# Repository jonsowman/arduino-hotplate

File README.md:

# Arduino Hotplate

An Arduino controlled hotplate for reflow soldering and rework.

Jon Sowman 2017

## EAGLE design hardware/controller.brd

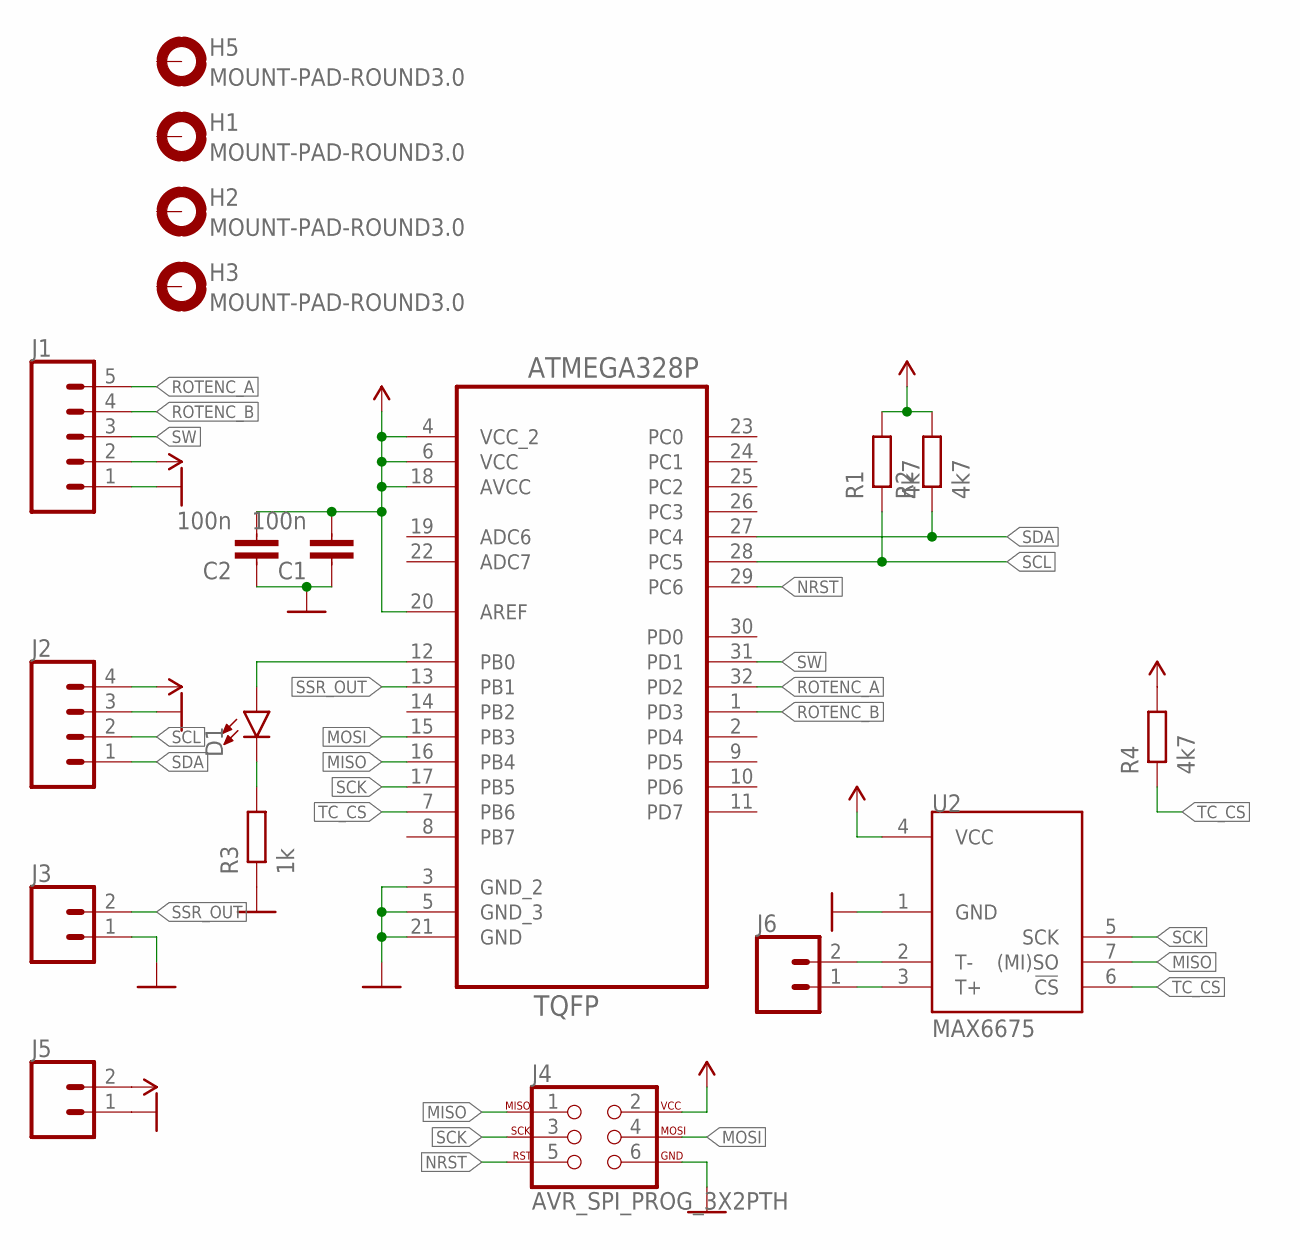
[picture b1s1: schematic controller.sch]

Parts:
C1, C2: 100n; C0603-N
D1: LED0603; LED-0603
H1, H2, H3, H5: MOUNT-PAD-ROUND3.0; 3,0-PAD
J1: CONN_05PTH_LONGPADS; 1X05_LONGPADS
J2: CONN_04LONGPADS; 1X04_LONGPADS
J3, J5, J6: CONN_02PTH3; 1X02_LONGPADS
J4: AVR_SPI_PROG_3X2PTH; 2X3
R1, R2, R4: 4k7; R0603-N
R3: 1k; R0603-N
U1: ATMEGA328P-AU; QFP80P900X900X120-32N
U2: MAX6675; SOIC8

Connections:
GND: C1.1, C2.1, J1.1, J2.3, J3.1, J4.6, J5.1, R3.1, U1.3 (GND_2), U1.5 (GND_3), U1.21 (GND), U2.1 (GND)
MISO: J4.1, U1.16 (PB4), U2.7 ((MI)SO)
MOSI: J4.4, U1.15 (PB3)
unnamed: D1.A, U1.12 (PB0)
unnamed: D1.C, R3.2
unnamed: J6.2, U2.2 (T-)
unnamed: J6.1, U2.3 (T+)
NRST: J4.5, U1.29 (PC6)
ROTENC_A: J1.5, U1.32 (PD2)
ROTENC_B: J1.4, U1.1 (PD3)
SCK: J4.3, U1.17 (PB5), U2.5 (SCK)
SCL: J2.2, R1.1, U1.28 (PC5)
SDA: J2.1, R2.1, U1.27 (PC4)
SSR_OUT: J3.2, U1.13 (PB1)
SW: J1.3, U1.31 (PD1)
TC_CS: R4.1, U1.7 (PB6), U2.6 (!CS)
VCC: C1.2, C2.2, J1.2, J2.4, J4.2, J5.2, R1.2, R2.2, R4.2, U1.4 (VCC_2), U1.6 (VCC), U1.18 (AVCC), U1.20 (AREF), U2.4 (VCC)

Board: 2 copper layers, 19 parts (0 on the bottom side), 17 nets, no tracks yet.

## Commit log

2017-03-16 initial
2017-03-16 stuff
2017-03-16 tidying firmware
2017-03-17 restructure
2017-03-17 enable integrator when within 10degC of target
2017-04-02 added max
2017-04-02 layout done

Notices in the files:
parts and their libraries:
SparkFun-Connectors: Licensing: Creative Commons ShareAlike 4.0 International - https://creativecommons.org/licenses/by-sa/4.0
